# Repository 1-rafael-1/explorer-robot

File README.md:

# explorer-robot

A tracked robot with LiDAR-based autonomous navigation and sensor-driven
obstacle avoidance, built in Rust on [Embassy](https://embassy.dev/) for the
RP2350B. It builds on hardware experience from
[simple-robot](https://github.com/1-rafael-1/simple-robot) and adds a 360° COIN-D6
LiDAR, two VL53L0X rangefinders, an ICM-20948 IMU, an ST7789 TFT with a resistive
touch panel, and a Grove Vision AI V2 camera — as much as fits on the custom PCB.

## Repository map

The repository is one tree with three Cargo workspaces, split by build target so
the robot's `thumbv8m` build never sees the RISC-V or host dependency graphs
([ADR-0040](docs/adr/0040-repo-and-build-layout.md)), plus the hardware sources
and the written material.

| Part | Directory | What it is | README |
|---|---|---|---|
| Robot firmware | `robot/`, root `Cargo.toml` | The `explorer-robot` Embassy firmware for the RP2350B (`thumbv8m.main-none-eabihf`) and its workspace crates: the Link Protocol, `LinkCore`, the drivers and the host-testable models | [robot](robot/README.md) |
| Bridge | `bridge/` | Its own workspace: the ESP32-C3 RISC-V firmware (`riscv32imc-unknown-none-elf`, `build-std`) that translates between the home network and the robot's UART1, and the HAL-free `bridge-core` rules | [bridge](bridge/README.md) |
| Remote | `remote/` | Its own host workspace (`x86_64-unknown-linux-gnu`): the `remote-daemon` relay, the shared `bridge-net` network edge, the two bench stubs and the static Remote App with its headless browser suite | [remote](remote/README.md) |
| Hardware | `hardware/` | FreeCAD chassis and running gear, KiCad schematic and PCB, BOM, print notes, assembly photos and safety notes — no Cargo target | [hardware](hardware/README.md) |
| Documentation | `docs/`, `CONTEXT.md` | The docs index, [architecture and data flow](docs/architecture.md), the [component pages](docs/README.md#component-pages), the [ADRs](docs/adr/), and the [domain glossary](CONTEXT.md) — no Cargo target | [docs](docs/README.md) |

The robot workspace holds `link-protocol` and `link-core` under
`robot/crates/link/`, the async drivers under `robot/crates/drivers/`, and the
pure models under `robot/crates/models/`; see the [robot package
README](robot/README.md) for the bucket map.

## Toolchain and dependencies

- **One Rust pin for the whole repository.** [`rust-toolchain.toml`](rust-toolchain.toml)
  selects channel **1.99.1** with the `rustfmt`, `clippy` and `rust-src`
  components and the `thumbv8m.main-none-eabihf` and
  `riscv32imc-unknown-none-elf` targets. There are no per-workspace toolchain
  files, so `rustup` applies the same pin inside `robot/`, `bridge/` and
  `remote/`.
- **The robot follows Embassy master.** The root manifest's
  `[patch.crates-io]` pins `embassy-rp` and its companion crates to one embassy
  commit, updated as a set.
- **The Bridge stays on the released `embassy-net` 0.9.1.** `esp-hal` 1.2.2,
  `esp-radio` 1.0.0-beta.1 and `esp-rtos` 0.4.0 pin the released embassy crates,
  whose `xarxa-driver` generation does not match embassy master's. The Bridge
  moves once the Espressif crates ship the newer generation; the reasoning is in
  [the Bridge dependency pin](docs/components/bridge.md#dependency-pin).
- **Nothing is packaged.** There are no published binaries, releases, OTA
  updates or installers. Build from source: `probe-rs` and SWD for the robot,
  `espflash` for the Bridge, `cargo` for the Remote.

## Quickstart

| Part | Start here | First command |
|---|---|---|
| Robot | [Robot page](docs/components/robot.md) | `cargo build --workspace --release --target thumbv8m.main-none-eabihf` from the repository root |
| Bridge | [Bridge page](docs/components/bridge.md) | `cd bridge && cargo build` |
| Remote | [Remote page](docs/components/remote.md) | `cd remote && cargo test --workspace` |
| Remote App | [app README](remote/app/README.md) | `.github/scripts/run_web_tests.sh` |
| Bench | [Bench page](docs/components/bench.md) | Wire the bench first, then `cd remote && cargo run -p bridge-stub -- --help` |

## Status

The robot firmware implements the drive subsystem, the COIN-D6 LiDAR perception
path, the panel UI and touch input, calibration, and the Link Task that owns
UART1 and the Link Port power. The LiDAR powers, warms and streams in Room
Scan; its baseline draw with the remote link up is about 320 mA. See the [robot
page](docs/components/robot.md#lidar-power-and-harness) for the power and
harness notes. The Bridge implements the network edge: the
Discovery Beacon, the HMAC preamble, the single-client gate, the credential
record and Pairing Token, Setup Mode with its portal, Bridge Presence and the
task watchdog. The Remote daemon implements discovery, the preamble, the Relay
and the `/ws` boundary. The Remote App is a static SPA in `remote/app/` that the
Relay serves at `/`: connection and pairing, the World Frame radar,
point-and-go, Activity/Events, Bridge status and the phone-landscape layout. Its
headless browser suite covers the static pages, the fake socket and the real
Relay + Bridge Stub chain, including reload reconstruction and the Result Report
(`run_web_tests.sh` and `run_real_chain.sh`); see the
[Remote page](docs/components/remote.md) and the
[app README](remote/app/README.md).

Still open: an async VL53L0X driver for the rangefinder pair (the firmware
ships an opt-in synthetic stub behind the `floor_drop_stub` feature), a Grove
Vision AI V2 driver (the PIO UART and switched 5 V branch are reserved), and
the manual real-phone pinch pass for the app.

## Read next

- [Documentation index](docs/README.md)
- [Architecture — repo map and data flow](docs/architecture.md)
- Component pages: [robot](docs/components/robot.md),
  [bridge](docs/components/bridge.md), [remote](docs/components/remote.md),
  [bench](docs/components/bench.md)
- [Domain glossary](CONTEXT.md) and the [architecture decision records](docs/adr/)
- [Hardware notes](hardware/README.md)

## License

MIT — see [LICENSE](LICENSE).

Portions are derived from the Raspberry Pi RP2350B Minimal reference design
(MIT); see [THIRD_PARTY_LICENSES.md](THIRD_PARTY_LICENSES.md) for details.

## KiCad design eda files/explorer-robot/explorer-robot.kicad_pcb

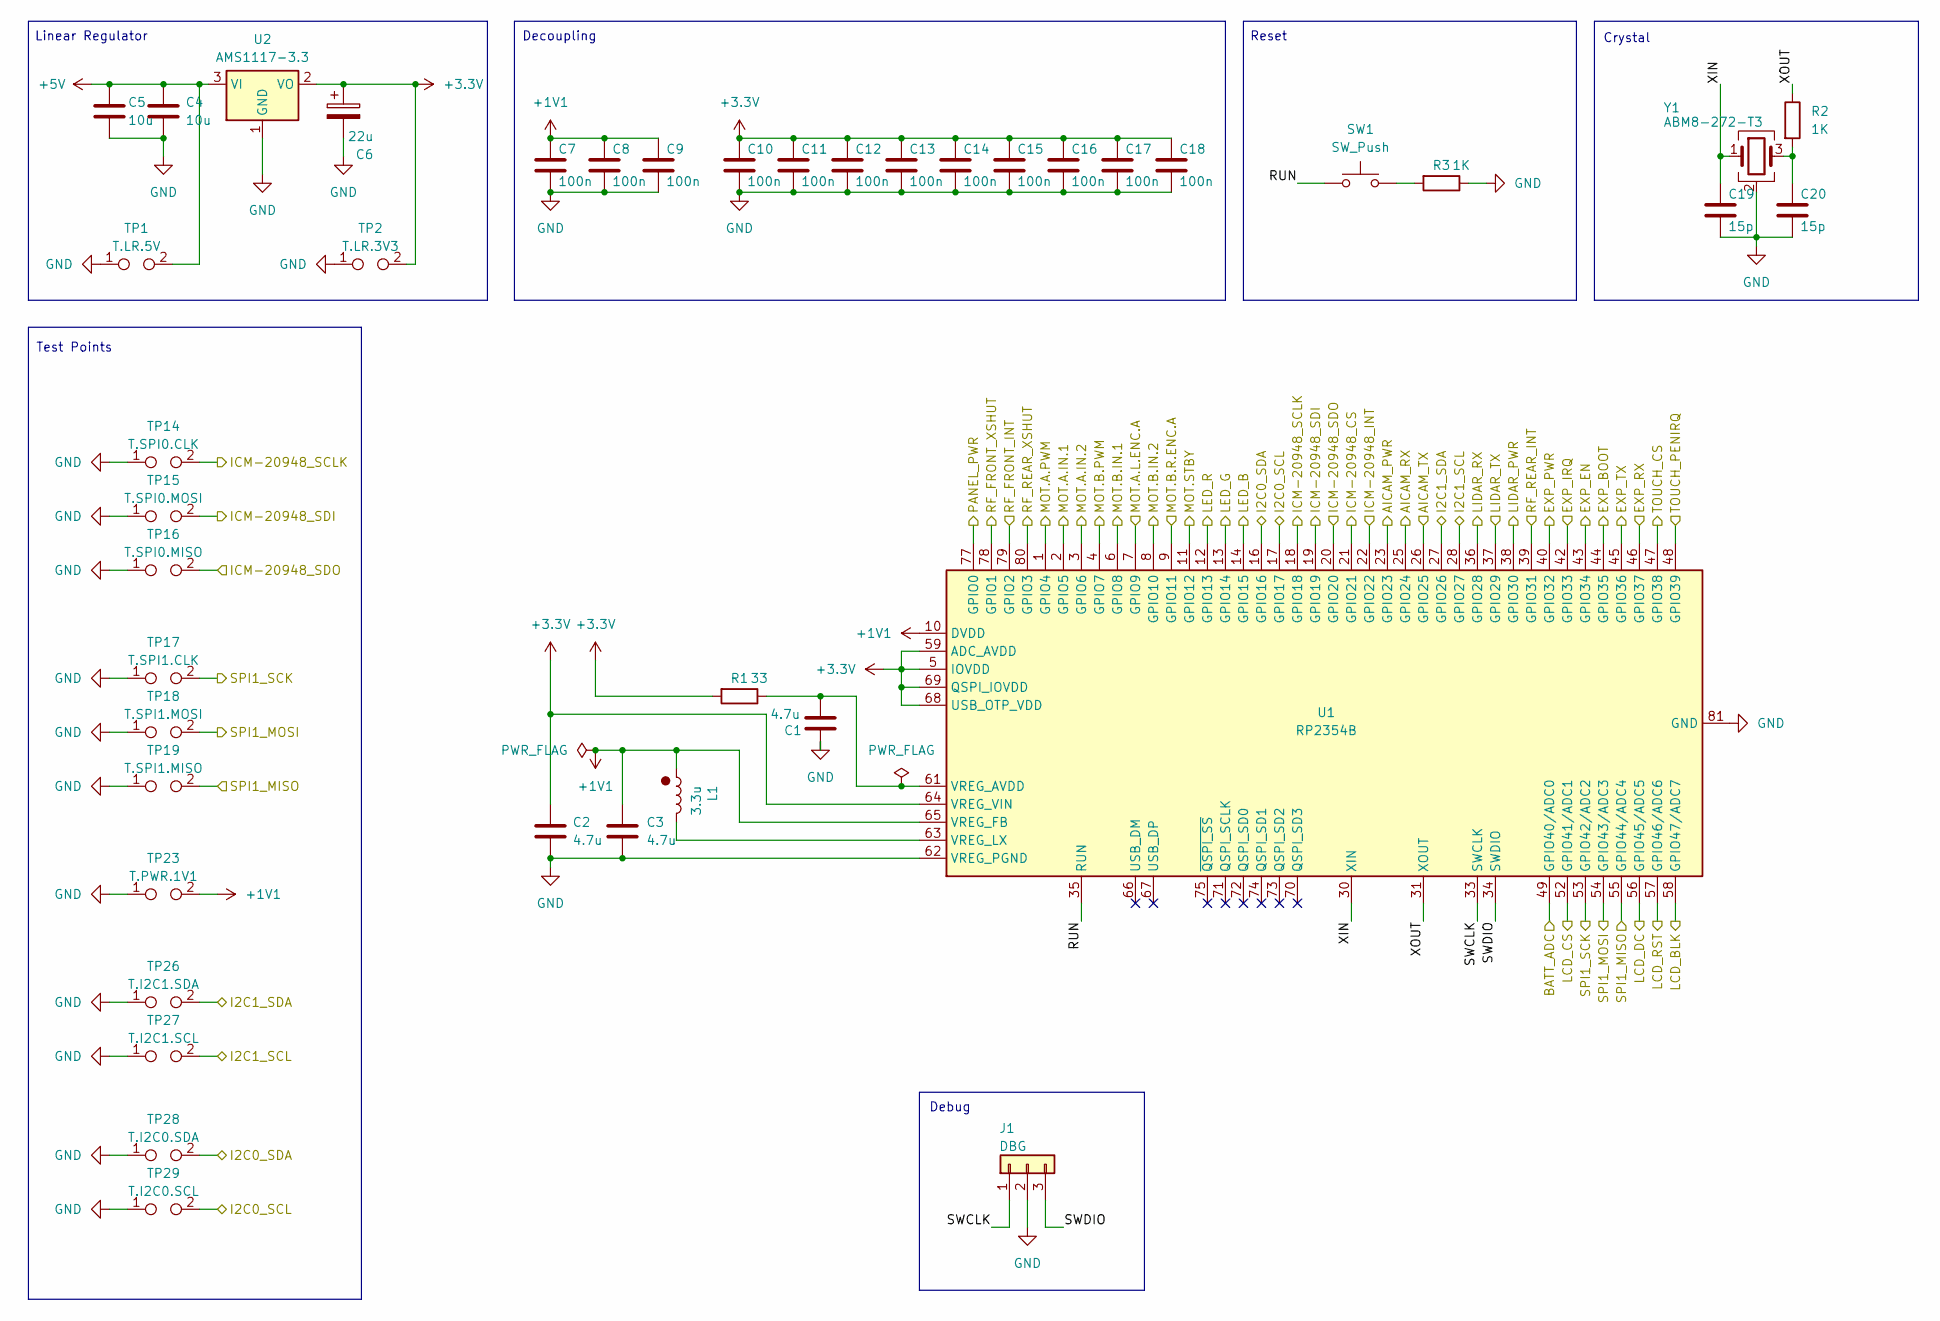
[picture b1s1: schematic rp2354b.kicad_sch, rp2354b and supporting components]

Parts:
C1, C2, C3: 4.7u; C_0402_1005Metric; MPN CL05A475MP5NRNC; LCSC C23733
C4, C5: 10u; C_0603_1608Metric; MPN CL10A106MA8NRNC; LCSC C96446
C6: 22u; CP_EIA-3216-18_Kemet-A; MPN TAJA226K010RNJ; LCSC C11366
C7, C8, C9, C10, C11, C12, C13, C14, C15, C16, C17, C18: 100n; C_0402_1005Metric; MPN CL05B104KO5NNNC; LCSC C1525
C19, C20: 15p; C_0402_1005Metric; MPN 0402CG150J500NT; LCSC C1548
J1: DBG; JST_SH_BM03B-SRSS-TB_1x03-1MP_P1.00mm_Vertical; MPN ZX-SH1.0-3PLT; LCSC C7430452
L1: 3.3u; abracon_aota-b201610s3r3-101-t; MPN AOTA-B201610S3R3-101-T; LCSC C42411119
R1: 33; R_0402_1005Metric; MPN 0402WGF330JTCE; LCSC C25105
R2, R3: 1K; R_0402_1005Metric; MPN 0402WGF1001TCE; LCSC C11702
SW1: SW_Push; SW_SPST_TS-1088-xR020; MPN TS-1088-AR02016; LCSC C720477
TP1: T.LR.5V; PinHeader_1x02_P2.54mm_Vertical
TP2: T.LR.3V3; PinHeader_1x02_P2.54mm_Vertical
TP14: T.SPI0.CLK; PinHeader_1x02_P2.54mm_Vertical
TP15: T.SPI0.MOSI; PinHeader_1x02_P2.54mm_Vertical
TP16: T.SPI0.MISO; PinHeader_1x02_P2.54mm_Vertical
TP17: T.SPI1.CLK; PinHeader_1x02_P2.54mm_Vertical
TP18: T.SPI1.MOSI; PinHeader_1x02_P2.54mm_Vertical
TP19: T.SPI1.MISO; PinHeader_1x02_P2.54mm_Vertical
TP23: T.PWR.1V1; PinHeader_1x02_P2.54mm_Vertical
TP26: T.I2C1.SDA; PinHeader_1x02_P2.54mm_Vertical
TP27: T.I2C1.SCL; PinHeader_1x02_P2.54mm_Vertical
TP28: T.I2C0.SDA; PinHeader_1x02_P2.54mm_Vertical
TP29: T.I2C0.SCL; PinHeader_1x02_P2.54mm_Vertical
U1: RP2354B; rpi_rp2350b_vias; MPN RP2354B; LCSC C39843328
U2: AMS1117-3.3; SOT-223-3_TabPin2; MPN AMS1117-3.3; LCSC C6186
Y1: ABM8-272-T3; CRYSTAL-SMD_4P-L3.2-W2.5-BL; MPN ABM8-272-T3; LCSC C20625731

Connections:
+1V1: C3.1, C7.1, C8.1, C9.1, L1.1, TP23.2, U1.10 (DVDD), U1.32 (DVDD), U1.51 (DVDD), U1.65 (VREG_FB)
+3.3V: C2.1, C6.1, C10.1, C11.1, C12.1, C13.1, C14.1, C15.1, C16.1, C17.1, C18.1, R1.2, TP2.2, U1.5 (IOVDD), U1.15 (IOVDD), U1.24 (IOVDD), U1.29 (IOVDD), U1.41 (IOVDD), U1.50 (IOVDD), U1.59 (ADC_AVDD), U1.60 (IOVDD), U1.64 (VREG_VIN), U1.68 (USB_OTP_VDD), U1.69 (QSPI_IOVDD), U1.76 (IOVDD), U2.2 (VO); also elsewhere on the board
+5V: C4.1, C5.1, TP1.2, U2.3 (VI); also elsewhere on the board
/AI CAM/AICAM_PWR: U1.23 (GPIO23); also elsewhere on the board
/AI CAM/AICAM_RX: U1.25 (GPIO24); also elsewhere on the board
/AI CAM/AICAM_TX: U1.26 (GPIO25); also elsewhere on the board
/Expansion/EXP_BOOT: U1.44 (GPIO35); also elsewhere on the board
/Expansion/EXP_EN: U1.43 (GPIO34); also elsewhere on the board
/Expansion/EXP_IRQ: U1.42 (GPIO33); also elsewhere on the board
/Expansion/EXP_PWR: U1.40 (GPIO32); also elsewhere on the board
/Expansion/EXP_RX: U1.46 (GPIO37); also elsewhere on the board
/Expansion/EXP_TX: U1.45 (GPIO36); also elsewhere on the board
/ICM-20948/ICM-20948_CS: U1.21 (GPIO21); also elsewhere on the board
/ICM-20948/ICM-20948_INT: U1.22 (GPIO22); also elsewhere on the board
/ICM-20948/ICM-20948_SCLK: TP14.2, U1.18 (GPIO18); also elsewhere on the board
/ICM-20948/ICM-20948_SDI: TP15.2, U1.19 (GPIO19); also elsewhere on the board
/ICM-20948/ICM-20948_SDO: TP16.2, U1.20 (GPIO20); also elsewhere on the board
/LIDAR/LIDAR_PWR: U1.38 (GPIO30); also elsewhere on the board
/LIDAR/LIDAR_RX: U1.36 (GPIO28); also elsewhere on the board
/LIDAR/LIDAR_TX: U1.37 (GPIO29); also elsewhere on the board
/Panel/LCD_BLK: U1.58 (GPIO47/ADC7); also elsewhere on the board
/Panel/LCD_CS: U1.52 (GPIO41/ADC1); also elsewhere on the board
/Panel/LCD_DC: U1.56 (GPIO45/ADC5); also elsewhere on the board
/Panel/LCD_RST: U1.57 (GPIO46/ADC6); also elsewhere on the board
/Panel/PANEL_PWR: U1.77 (GPIO0); also elsewhere on the board
/Panel/SPI1_MISO: TP19.2, U1.55 (GPIO44/ADC4); also elsewhere on the board
/Panel/SPI1_MOSI: TP18.2, U1.54 (GPIO43/ADC3); also elsewhere on the board
/Panel/SPI1_SCK: TP17.2, U1.53 (GPIO42/ADC2); also elsewhere on the board
/Panel/TOUCH_CS: U1.47 (GPIO38); also elsewhere on the board
/Panel/TOUCH_PENIRQ: U1.48 (GPIO39); also elsewhere on the board
/Power and Battery/BATT_ADC: U1.49 (GPIO40/ADC0); also elsewhere on the board
/RGB LED/LED_B: U1.14 (GPIO15); also elsewhere on the board
/RGB LED/LED_G: U1.13 (GPIO14); also elsewhere on the board
/RGB LED/LED_R: U1.12 (GPIO13); also elsewhere on the board
/Rangefinders/I2C0_SCL: TP29.2, U1.17 (GPIO17); also elsewhere on the board
/Rangefinders/I2C0_SDA: TP28.2, U1.16 (GPIO16); also elsewhere on the board
/Rangefinders/I2C1_SCL: TP27.2, U1.28 (GPIO27); also elsewhere on the board
/Rangefinders/I2C1_SDA: TP26.2, U1.27 (GPIO26); also elsewhere on the board
/Rangefinders/RF_FRONT_INT: U1.79 (GPIO2); also elsewhere on the board
/Rangefinders/RF_FRONT_XSHUT: U1.78 (GPIO1); also elsewhere on the board
/Rangefinders/RF_REAR_INT: U1.39 (GPIO31); also elsewhere on the board
/Rangefinders/RF_REAR_XSHUT: U1.80 (GPIO3); also elsewhere on the board
/TB6612FNG and encoders/MOT.A.IN.1: U1.2 (GPIO5); also elsewhere on the board
/TB6612FNG and encoders/MOT.A.IN.2: U1.3 (GPIO6); also elsewhere on the board
/TB6612FNG and encoders/MOT.A.L.ENC.A: U1.7 (GPIO9); also elsewhere on the board
/TB6612FNG and encoders/MOT.A.PWM: U1.1 (GPIO4); also elsewhere on the board
/TB6612FNG and encoders/MOT.B.IN.1: U1.6 (GPIO8); also elsewhere on the board
/TB6612FNG and encoders/MOT.B.IN.2: U1.8 (GPIO10); also elsewhere on the board
/TB6612FNG and encoders/MOT.B.PWM: U1.4 (GPIO7); also elsewhere on the board
/TB6612FNG and encoders/MOT.B.R.ENC.A: U1.9 (GPIO11); also elsewhere on the board
/TB6612FNG and encoders/MOT.STBY: U1.11 (GPIO12); also elsewhere on the board
/rp2354b/RUN: SW1.1, U1.35 (RUN)
/rp2354b/SWCLK: J1.1, U1.33 (SWCLK)
/rp2354b/SWDIO: J1.3, U1.34 (SWDIO)
/rp2354b/XIN: C19.1, U1.30 (XIN), Y1.1
/rp2354b/XOUT: R2.1, U1.31 (XOUT)
GND: C1.2, C2.2, C3.2, C4.2, C5.2, C6.2, C7.2, C8.2, C9.2, C10.2, C11.2, C12.2, C13.2, C14.2, C15.2, C16.2, C17.2, C18.2, C19.2, C20.2, J1.2, R3.1, TP1.1, TP2.1, TP14.1, TP15.1, TP16.1, TP17.1, TP18.1, TP19.1, TP23.1, TP26.1, TP27.1, TP28.1, TP29.1, U1.62 (VREG_PGND), U1.81 (GND), U2.1 (GND), Y1.2 (G), Y1.4 (G); also elsewhere on the board
unnamed: C20.1, R2.2, Y1.3
unnamed: R3.2, SW1.2
unnamed: C1.1, R1.1, U1.61 (VREG_AVDD)
unnamed: L1.2, U1.63 (VREG_LX)

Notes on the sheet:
Reset
Debug
Linear Regulator
Test Points
Decoupling
Crystal

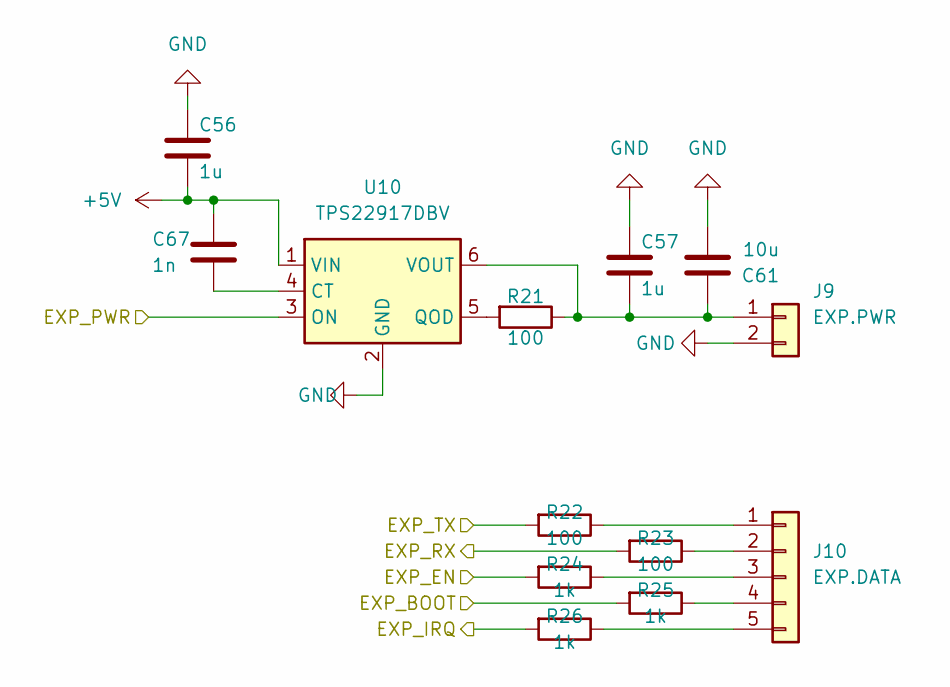
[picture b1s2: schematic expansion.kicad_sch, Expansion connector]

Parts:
C56, C57: 1u; C_0603_1608Metric; MPN CL10A105KB8NNNC; LCSC C15849
C61: 10u; C_0805_2012Metric; MPN CL21A106KAYNNNE; LCSC C15850
C67: 1n; C_0603_1608Metric; MPN CL10B102KB8NNNC; LCSC C1588
J9: EXP.PWR; JST_PH_B2B-PH-K_1x02_P2.00mm_Vertical
J10: EXP.DATA; JST_PH_B5B-PH-K_1x05_P2.00mm_Vertical
R21, R22, R23: 100; R_0603_1608Metric; MPN 0603WAF1000T5E; LCSC C22775
R24, R25, R26: 1k; R_0603_1608Metric; MPN 0603WAF1001T5E; LCSC C21190
U10: TPS22917DBV; SOT-23-6; MPN TPS22917DBVR; LCSC C2681320

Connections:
+5V: C56.2, C67.2, U10.1 (VIN); also elsewhere on the board
/Expansion/EXP_BOOT: R25.2; also elsewhere on the board
/Expansion/EXP_EN: R24.2; also elsewhere on the board
/Expansion/EXP_IRQ: R26.2; also elsewhere on the board
/Expansion/EXP_PWR: U10.3 (ON); also elsewhere on the board
/Expansion/EXP_RX: R23.2; also elsewhere on the board
/Expansion/EXP_TX: R22.2; also elsewhere on the board
GND: C56.1, C57.1, C61.2, J9.2, U10.2 (GND); also elsewhere on the board
unnamed: C57.2, C61.1, J9.1, R21.1, U10.6 (VOUT)
unnamed: J10.1, R22.1
unnamed: J10.2, R23.1
unnamed: J10.3, R24.1
unnamed: J10.4, R25.1
unnamed: J10.5, R26.1
unnamed: C67.1, U10.4 (CT)
unnamed: R21.2, U10.5 (QOD)

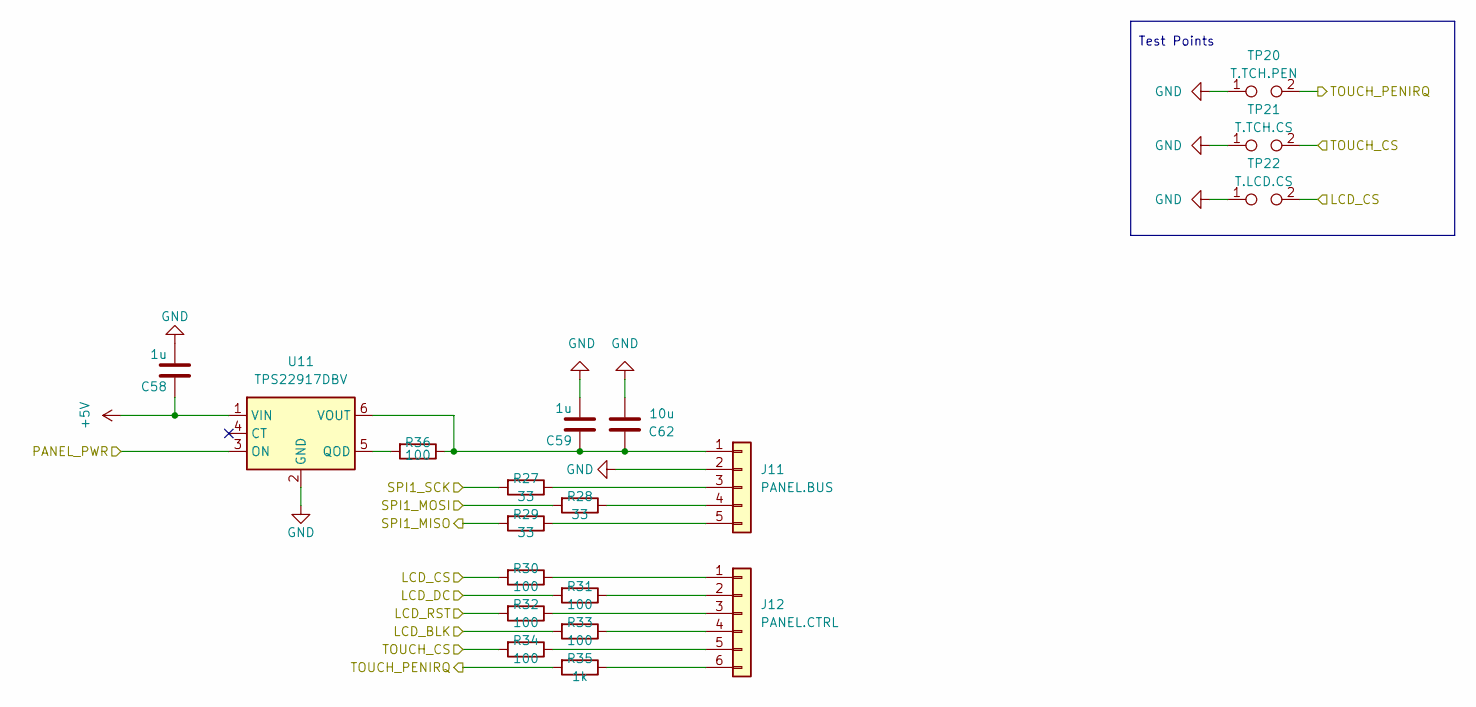
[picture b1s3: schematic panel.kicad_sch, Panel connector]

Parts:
C58, C59: 1u; C_0603_1608Metric; MPN CL10A105KB8NNNC; LCSC C15849
C62: 10u; C_0805_2012Metric; MPN CL21A106KAYNNNE; LCSC C15850
J11: PANEL.BUS; JST_PH_B5B-PH-K_1x05_P2.00mm_Vertical
J12: PANEL.CTRL; JST_PH_B6B-PH-K_1x06_P2.00mm_Vertical
R27, R28, R29: 33; R_0603_1608Metric; MPN 0603WAF330JT5E; LCSC C23140
R30, R31, R32, R33, R34, R36: 100; R_0603_1608Metric; MPN 0603WAF1000T5E; LCSC C22775
R35: 1k; R_0603_1608Metric; MPN 0603WAF1001T5E; LCSC C21190
TP20: T.TCH.PEN; PinHeader_1x02_P2.54mm_Vertical
TP21: T.TCH.CS; PinHeader_1x02_P2.54mm_Vertical
TP22: T.LCD.CS; PinHeader_1x02_P2.54mm_Vertical
U11: TPS22917DBV; SOT-23-6; MPN TPS22917DBVR; LCSC C2681320

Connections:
+5V: C58.1, U11.1 (VIN); also elsewhere on the board
/Panel/LCD_BLK: R33.2; also elsewhere on the board
/Panel/LCD_CS: R30.2, TP22.2; also elsewhere on the board
/Panel/LCD_DC: R31.2; also elsewhere on the board
/Panel/LCD_RST: R32.2; also elsewhere on the board
/Panel/PANEL_PWR: U11.3 (ON); also elsewhere on the board
/Panel/SPI1_MISO: R29.2; also elsewhere on the board
/Panel/SPI1_MOSI: R28.2; also elsewhere on the board
/Panel/SPI1_SCK: R27.2; also elsewhere on the board
/Panel/TOUCH_CS: R34.2, TP21.2; also elsewhere on the board
/Panel/TOUCH_PENIRQ: R35.2, TP20.2; also elsewhere on the board
GND: C58.2, C59.2, C62.2, J11.2, TP20.1, TP21.1, TP22.1, U11.2 (GND); also elsewhere on the board
unnamed: C59.1, C62.1, J11.1, R36.1, U11.6 (VOUT)
unnamed: J11.3, R27.1
unnamed: J11.4, R28.1
unnamed: J11.5, R29.1
unnamed: J12.1, R30.1
unnamed: J12.2, R31.1
unnamed: J12.3, R32.1
unnamed: J12.4, R33.1
unnamed: J12.5, R34.1
unnamed: J12.6, R35.1
unnamed 116: U11.4 (CT); also elsewhere on the board
unnamed: R36.2, U11.5 (QOD)

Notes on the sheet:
Test Points

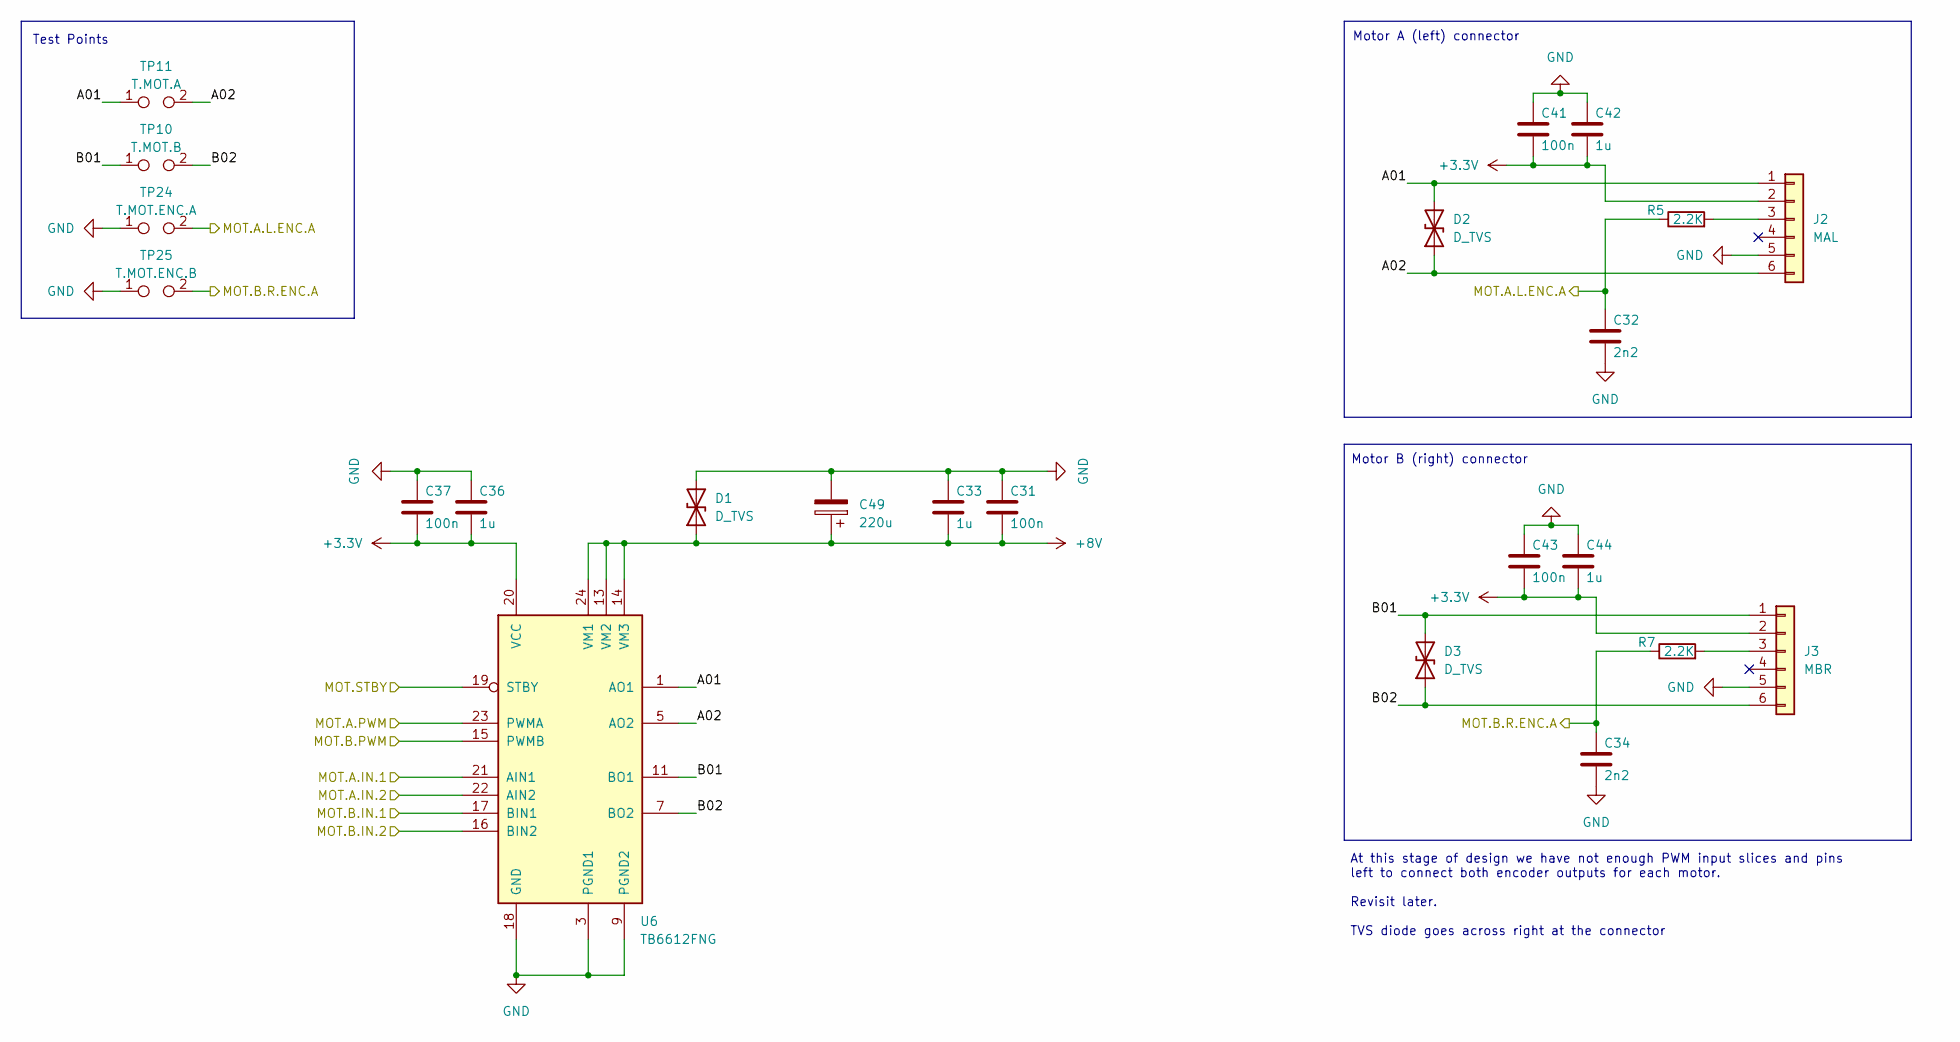
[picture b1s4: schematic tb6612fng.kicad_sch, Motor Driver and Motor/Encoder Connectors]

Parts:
C31, C37, C41, C43: 100n; C_0603_1608Metric; MPN CC0603KRX7R9BB104; LCSC C14663
C32, C34: 2n2; C_0603_1608Metric; MPN 0603B222K500NT; LCSC C1604
C33, C36, C42, C44: 1u; C_0603_1608Metric; MPN CL10A105KB8NNNC; LCSC C15849
C49: 220u; CP_Elec_6.3x7.7; MPN 217EC0037; LCSC C42371908
D1, D2, D3: D_TVS; D_SMA; MPN P4SMA10CA; LCSC C20602531
J2: MAL; JST_PH_B6B-PH-K_1x06_P2.00mm_Vertical
J3: MBR; JST_PH_B6B-PH-K_1x06_P2.00mm_Vertical
R5, R7: 2.2K; R_0603_1608Metric; MPN 0603WAF2201T5E; LCSC C4190
TP10: T.MOT.B; PinHeader_1x02_P2.54mm_Vertical
TP11: T.MOT.A; PinHeader_1x02_P2.54mm_Vertical
TP24: T.MOT.ENC.A; PinHeader_1x02_P2.54mm_Vertical
TP25: T.MOT.ENC.B; PinHeader_1x02_P2.54mm_Vertical
U6: TB6612FNG; SSOP-24_5.3x8.2mm_P0.65mm; MPN TB6612FNG(O,C,8,EL; LCSC C141517

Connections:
+3.3V: C36.2, C37.2, C41.2, C42.2, C43.2, C44.2, J2.2, J3.2, U6.20 (VCC); also elsewhere on the board
+8V: C31.2, C33.2, C49.1, D1.1 (A1), U6.13 (VM2), U6.14 (VM3), U6.24 (VM1); also elsewhere on the board
/TB6612FNG and encoders/A01: D2.2 (A2), J2.1, TP11.1, U6.1 (AO1), U6.2 (AO1)
/TB6612FNG and encoders/A02: D2.1 (A1), J2.6, TP11.2, U6.5 (AO2), U6.6 (AO2)
/TB6612FNG and encoders/B01: D3.2 (A2), J3.1, TP10.1, U6.11 (BO1), U6.12 (BO1)
/TB6612FNG and encoders/B02: D3.1 (A1), J3.6, TP10.2, U6.7 (BO2), U6.8 (BO2)
/TB6612FNG and encoders/MOT.A.IN.1: U6.21 (AIN1); also elsewhere on the board
/TB6612FNG and encoders/MOT.A.IN.2: U6.22 (AIN2); also elsewhere on the board
/TB6612FNG and encoders/MOT.A.L.ENC.A: C32.1, R5.1, TP24.2; also elsewhere on the board
/TB6612FNG and encoders/MOT.A.PWM: U6.23 (PWMA); also elsewhere on the board
/TB6612FNG and encoders/MOT.B.IN.1: U6.17 (BIN1); also elsewhere on the board
/TB6612FNG and encoders/MOT.B.IN.2: U6.16 (BIN2); also elsewhere on the board
/TB6612FNG and encoders/MOT.B.PWM: U6.15 (PWMB); also elsewhere on the board
/TB6612FNG and encoders/MOT.B.R.ENC.A: C34.1, R7.1, TP25.2; also elsewhere on the board
/TB6612FNG and encoders/MOT.STBY: U6.19 (STBY); also elsewhere on the board
GND: C31.1, C32.2, C33.1, C34.2, C36.1, C37.1, C41.1, C42.1, C43.1, C44.1, C49.2, D1.2 (A2), J2.5, J3.5, TP24.1, TP25.1, U6.3 (PGND1), U6.4 (PGND1), U6.9 (PGND2), U6.10 (PGND2), U6.18 (GND); also elsewhere on the board
unnamed: J2.3, R5.2
unnamed: J3.3, R7.2

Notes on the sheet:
Motor A (left) connector
Test Points
Motor B (right) connector
At this stage of design we have not enough PWM input slices and pins left to connect both encoder outputs for each motor. Revisit later. TVS diode goes across right at the connector

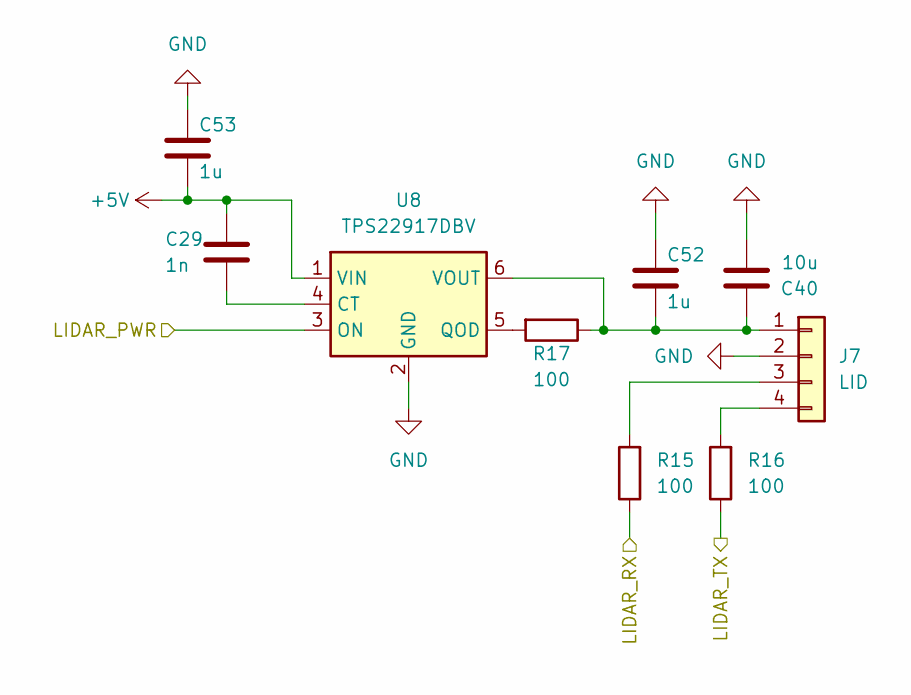
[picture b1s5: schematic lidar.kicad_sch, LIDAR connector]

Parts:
C29: 1n; C_0603_1608Metric; MPN CL10B102KB8NNNC; LCSC C1588
C40: 10u; C_0805_2012Metric; MPN CL21A106KAYNNNE; LCSC C15850
C52, C53: 1u; C_0603_1608Metric; MPN CL10A105KB8NNNC; LCSC C15849
J7: LID; JST_PH_B4B-PH-K_1x04_P2.00mm_Vertical
R15, R16, R17: 100; R_0603_1608Metric; MPN 0603WAF1000T5E; LCSC C22775
U8: TPS22917DBV; SOT-23-6; MPN TPS22917DBVR; LCSC C2681320

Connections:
+5V: C29.2, C53.2, U8.1 (VIN); also elsewhere on the board
/LIDAR/LIDAR_PWR: U8.3 (ON); also elsewhere on the board
/LIDAR/LIDAR_RX: R15.1; also elsewhere on the board
/LIDAR/LIDAR_TX: R16.1; also elsewhere on the board
GND: C40.2, C52.1, C53.1, J7.2, U8.2 (GND); also elsewhere on the board
unnamed: C40.1, C52.2, J7.1, R17.1, U8.6 (VOUT)
unnamed: J7.3, R15.2
unnamed: J7.4, R16.2
unnamed: C29.1, U8.4 (CT)
unnamed: R17.2, U8.5 (QOD)

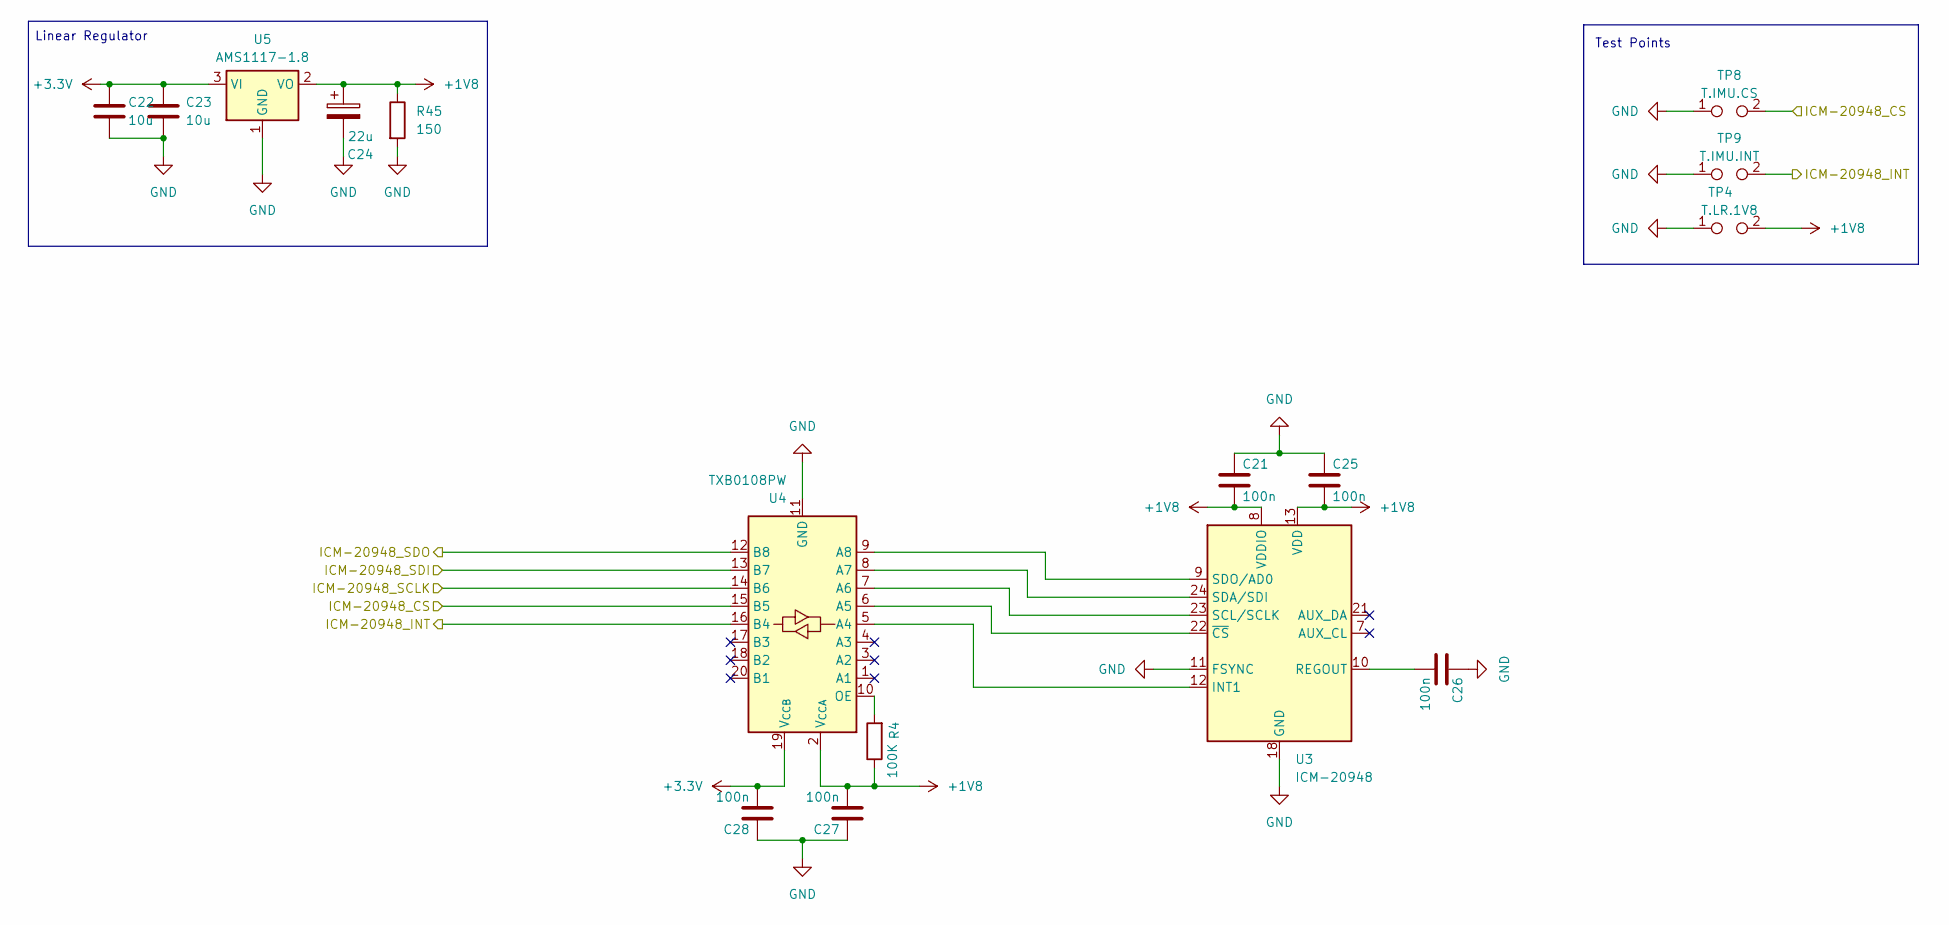
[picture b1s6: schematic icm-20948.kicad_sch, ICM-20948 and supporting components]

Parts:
C21, C25, C26, C27, C28: 100n; C_0603_1608Metric; MPN CC0603KRX7R9BB104; LCSC C14663
C22, C23: 10u; C_0603_1608Metric; MPN CL10A106KP8NNNC; LCSC C19702
C24: 22u; CP_EIA-3216-18_Kemet-A; MPN TAJA226K010RNJ; LCSC C11366
R4: 100K; R_0402_1005Metric; MPN 0402WGF1003TCE; LCSC C25741
R45: 150; R_0603_1608Metric; MPN 0603WAF1500T5E; LCSC C22808
TP4: T.LR.1V8; PinHeader_1x02_P2.54mm_Vertical
TP8: T.IMU.CS; PinHeader_1x02_P2.54mm_Vertical
TP9: T.IMU.INT; PinHeader_1x02_P2.54mm_Vertical
U3: ICM-20948; QFN-24_L3.0-W3.0-P0.40-BL-EP; MPN ICM-20948; LCSC C726001
U4: TXB0108PW; TSSOP-20_4.4x6.5mm_P0.65mm; MPN TXB0108PWR; LCSC C53406
U5: AMS1117-1.8; SOT-223-3_TabPin2; MPN AMS1117-1.8; LCSC C347220

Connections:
+1V8: C21.2, C24.1, C25.2, C27.2, R4.1, R45.1, TP4.2, U3.8 (VDDIO), U3.13 (VDD), U4.2 (V_{CCA}), U5.2 (VO)
+3.3V: C22.1, C23.1, C28.2, U4.19 (V_{CCB}), U5.3 (VI); also elsewhere on the board
/ICM-20948/ICM-20948_CS: TP8.2, U4.15 (B5); also elsewhere on the board
/ICM-20948/ICM-20948_INT: TP9.2, U4.16 (B4); also elsewhere on the board
/ICM-20948/ICM-20948_SCLK: U4.14 (B6); also elsewhere on the board
/ICM-20948/ICM-20948_SDI: U4.13 (B7); also elsewhere on the board
/ICM-20948/ICM-20948_SDO: U4.12 (B8); also elsewhere on the board
GND: C21.1, C22.2, C23.2, C24.2, C25.1, C26.1, C27.1, C28.1, R45.2, TP4.1, TP8.1, TP9.1, U3.11 (FSYNC), U3.18 (GND), U3.20 (GND), U4.1 (A1), U4.3 (A2), U4.4 (A3), U4.11 (GND), U4.17 (B3), U4.18 (B2), U4.20 (B1), U5.1 (GND); also elsewhere on the board
unnamed: U3.12 (INT1), U4.5 (A4)
unnamed: C26.2, U3.10 (REGOUT)
unnamed: U3.23 (SCL/SCLK), U4.7 (A6)
unnamed: U3.24 (SDA/SDI), U4.8 (A7)
unnamed: U3.9 (SDO/AD0), U4.9 (A8)
unnamed: U3.22 (~CS), U4.6 (A5)
unnamed: R4.2, U4.10 (OE)

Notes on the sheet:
Test Points
Linear Regulator

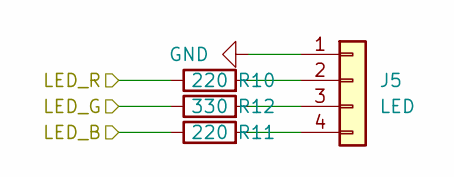
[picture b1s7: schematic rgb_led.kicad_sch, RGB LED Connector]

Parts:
J5: LED; JST_PH_B4B-PH-K_1x04_P2.00mm_Vertical
R10, R11: 220; R_0603_1608Metric; MPN 0603WAF2200T5E; LCSC C22962
R12: 330; R_0603_1608Metric; MPN 0603WAF3300T5E; LCSC C23138

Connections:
/RGB LED/LED_B: R11.1; also elsewhere on the board
/RGB LED/LED_G: R12.1; also elsewhere on the board
/RGB LED/LED_R: R10.1; also elsewhere on the board
GND: J5.1; also elsewhere on the board
unnamed: J5.2, R10.2
unnamed: J5.3, R12.2
unnamed: J5.4, R11.2

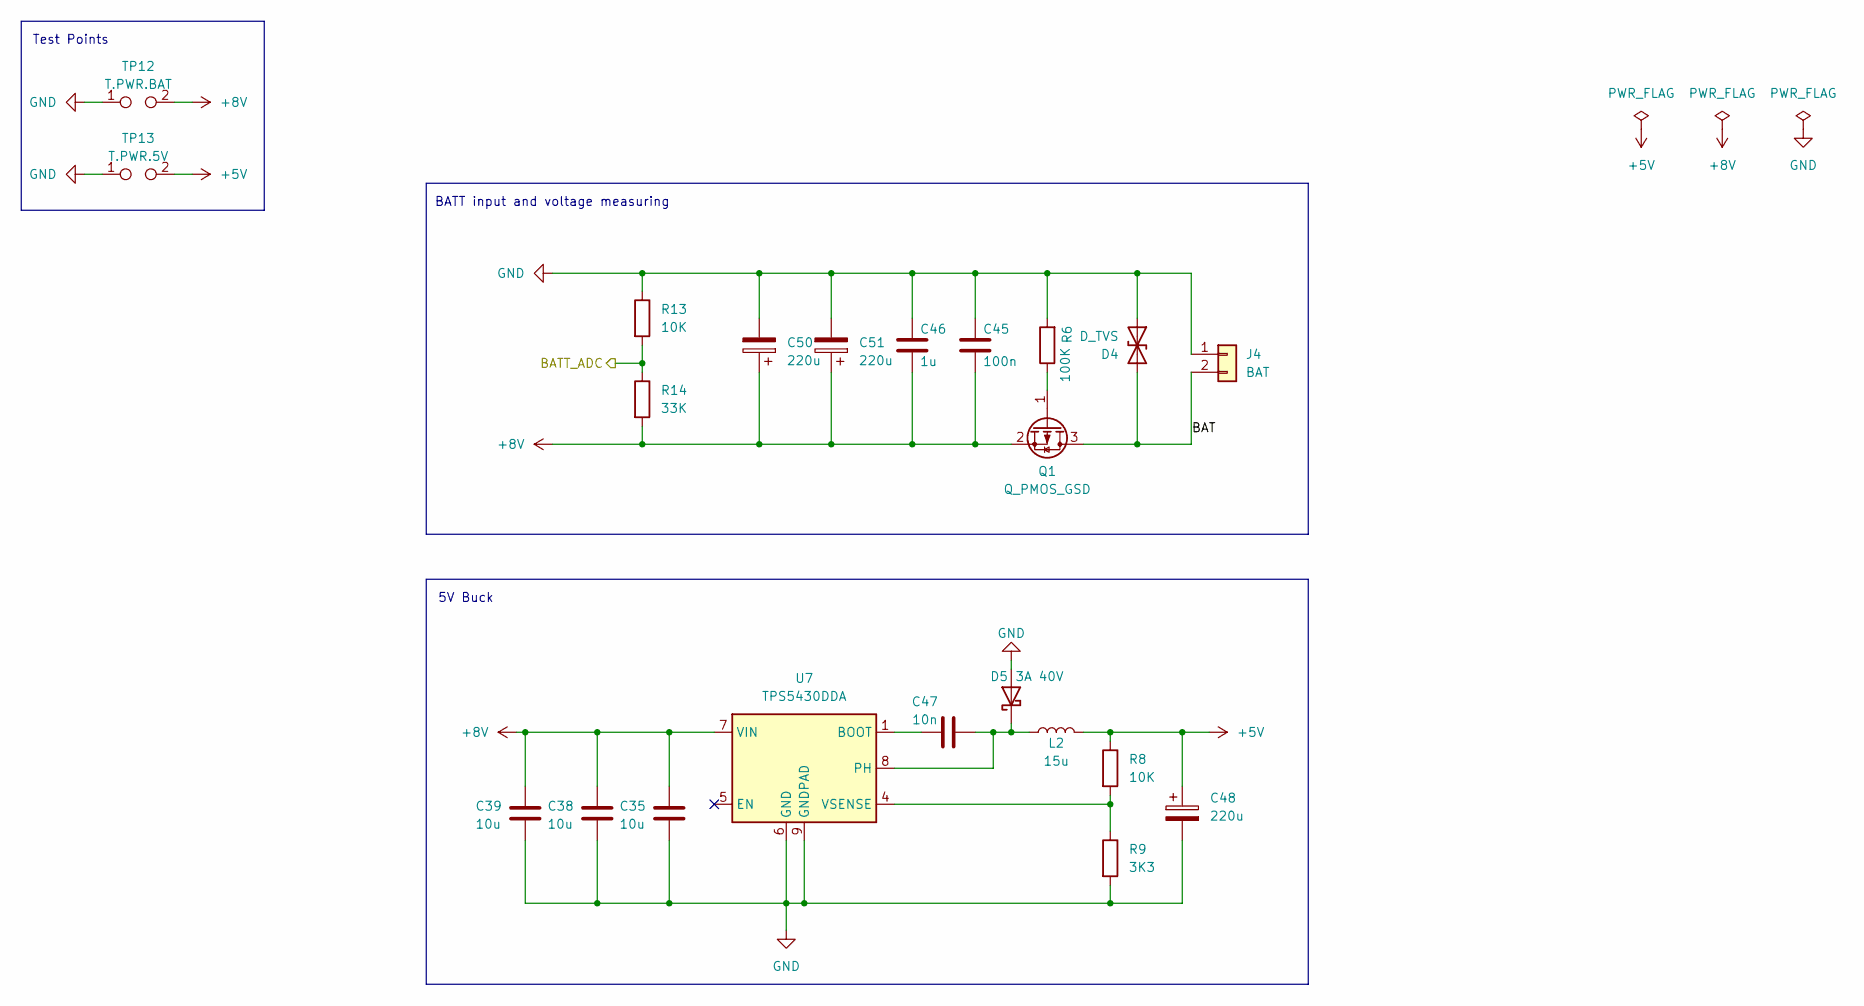
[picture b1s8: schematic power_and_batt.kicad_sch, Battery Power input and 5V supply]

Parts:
C35, C38, C39: 10u; C_0805_2012Metric; MPN CL21A106KAYNNNE; LCSC C15850
C45: 100n; C_0603_1608Metric; MPN CC0603KRX7R9BB104; LCSC C14663
C46: 1u; C_0603_1608Metric; MPN CL10A105KB8NNNC; LCSC C15849
C47: 10n; C_0805_2012Metric; MPN CL21B103KBANNNC; LCSC C1710
C48, C50, C51: 220u; CP_Elec_6.3x7.7; MPN 217EC0037; LCSC C42371908
D4: D_TVS; D_SMA; MPN P4SMA10CA; LCSC C20602531
D5: 3A 40V; D_SMA; MPN SS34; LCSC C8678
J4: BAT; JST_XH_B2B-XH-A_1x02_P2.50mm_Vertical
L2: 15u; IND-SMD_L7.1-W6.6_SLO0618H; MPN SLO0630H150MTT; LCSC C182182
Q1: Q_PMOS_GSD; SOT-23; MPN AO3407A; LCSC C15155
R6: 100K; R_0402_1005Metric; MPN 0402WGF1003TCE; LCSC C25741
R8, R13: 10K; R_0603_1608Metric; MPN 0603WAF1002T5E; LCSC C25804
R9: 3K3; R_0603_1608Metric; MPN 0603WAF3301T5E; LCSC C22978
R14: 33K; R_0603_1608Metric; MPN 0603WAF3302T5E; LCSC C4216
TP12: T.PWR.BAT; PinHeader_1x02_P2.54mm_Vertical
TP13: T.PWR.5V; PinHeader_1x02_P2.54mm_Vertical
U7: TPS5430DDA; TI_SO-PowerPAD-8_ThermalVias; MPN TPS5430DDAR; LCSC C9864

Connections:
+5V: C48.1, L2.2, R8.1, TP13.2; also elsewhere on the board
+8V: C35.1, C38.1, C39.1, C45.2, C46.2, C50.1, C51.1, Q1.2 (S), R14.2, TP12.2, U7.7 (VIN); also elsewhere on the board
/Power and Battery/BAT: D4.2 (A2), J4.2, Q1.3 (D)
/Power and Battery/BATT_ADC: R13.2, R14.1; also elsewhere on the board
GND: C35.2, C38.2, C39.2, C45.1, C46.1, C48.2, C50.2, C51.2, D4.1 (A1), D5.2 (A), J4.1, R6.2, R9.2, R13.1, TP12.1, TP13.1, U7.6 (GND), U7.9 (GNDPAD); also elsewhere on the board
unnamed: C47.2, D5.1 (K), L2.1, U7.8 (PH)
unnamed: Q1.1 (G), R6.1
unnamed: C47.1, U7.1 (BOOT)
unnamed: R8.2, R9.1, U7.4 (VSENSE)

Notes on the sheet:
BATT input and voltage measuring
5V Buck
Test Points
